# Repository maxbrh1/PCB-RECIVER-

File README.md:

# PCB-RECIVER-

ONETAP Reciver is my pcb

CC1101EM_868_915MHz_3_0_0 Is Ti's refrence design with the cc1101

Please see Schematic Onetap reciver.pdf

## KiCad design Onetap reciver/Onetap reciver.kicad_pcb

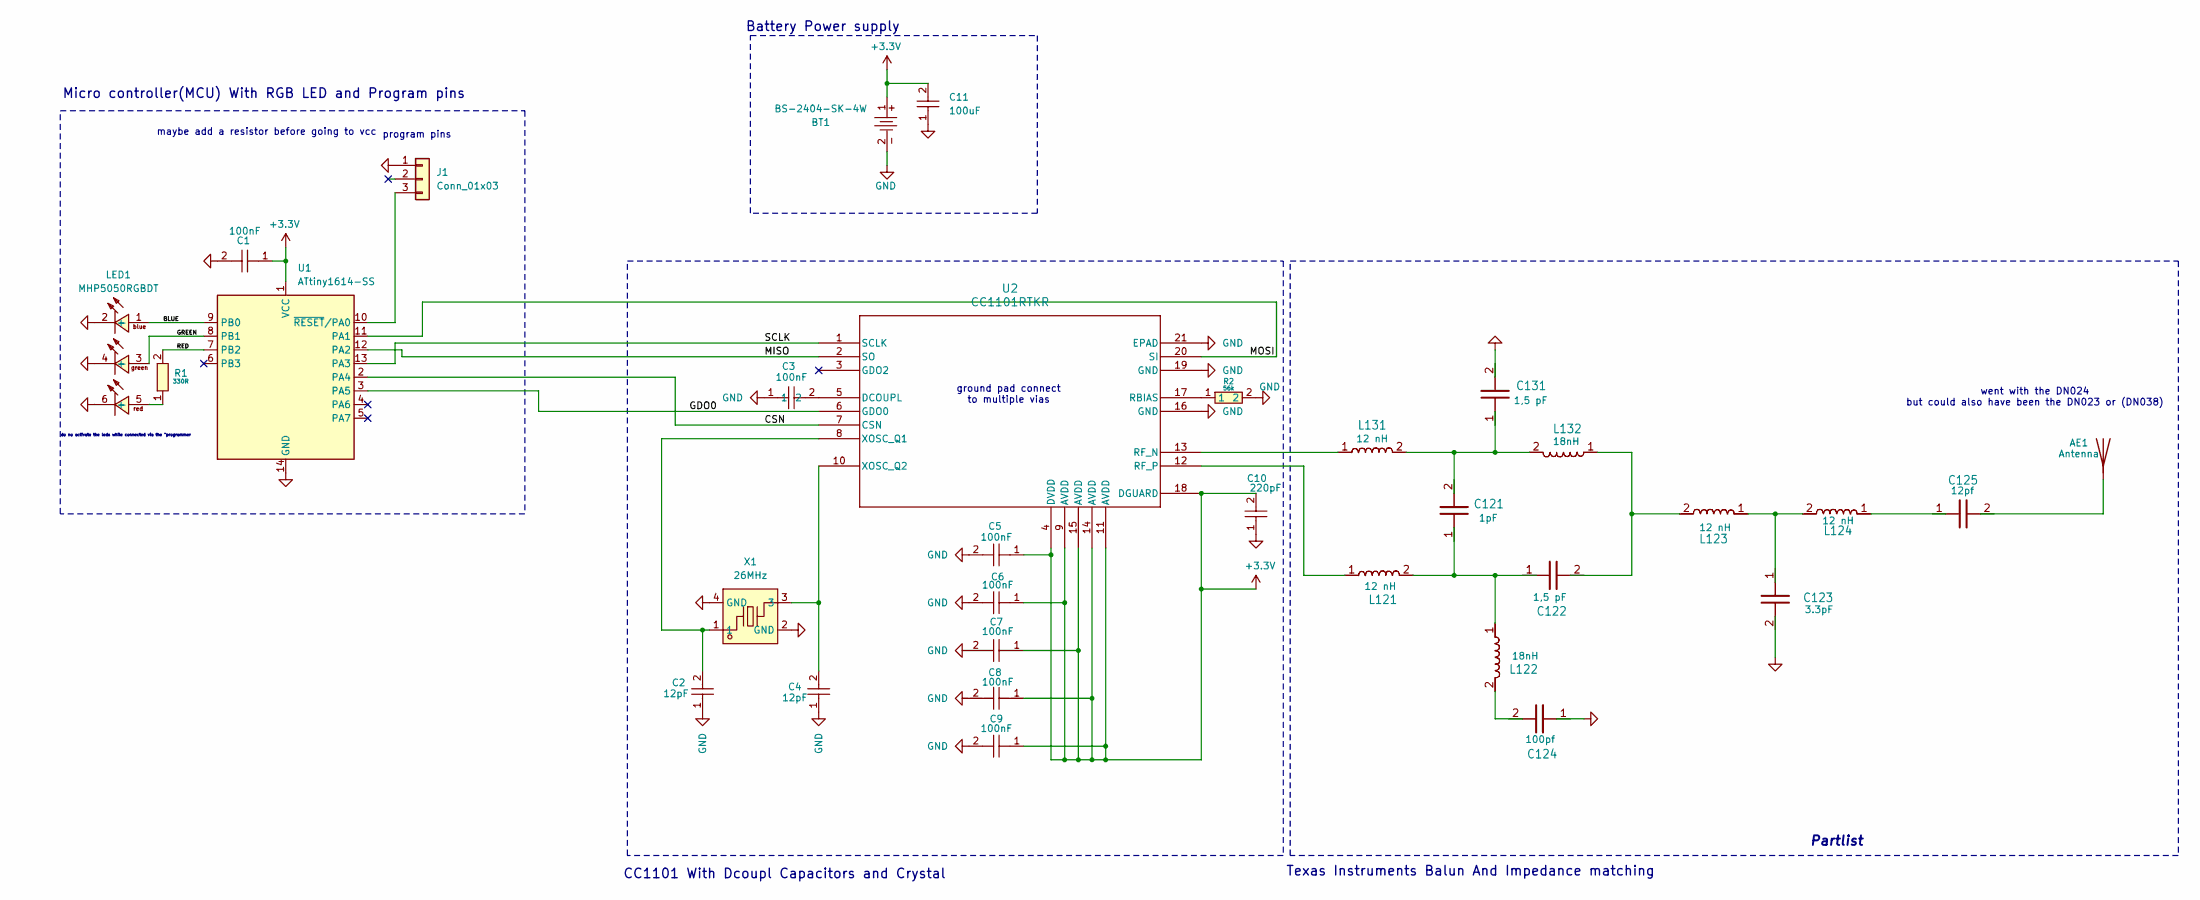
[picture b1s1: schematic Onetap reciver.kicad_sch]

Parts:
AE1: Antenna; DN024
BT1: BS-2404-SK-4W; BAT-SMD_BS-2404-SK-4W; MPN BS-2404-SK-4W; LCSC Part C19089132
C1, C3: 100nF; C0603; MPN CL10B104KB8NNNC; LCSC Part C1591
C2, C4: 12pF; C0603; MPN CL10C120JB8NNNC; LCSC Part C38523
C5, C6, C7, C8, C9: 100nF; G-155_MUR; DigiKey Part Number 490-6321-2-ND - Tape & Reel (TR) 490-63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
C10: 220pF; C0603; MPN CL10B221KB8NNNC; LCSC Part C1603
C11: 100uF; C1206; MPN CL31A107MQHNNNE; LCSC Part C15008
C121: 1pF; TI_0402_RF; Part Name C_1P0_0402_NP0_C_50
C122, C131: 1,5 pF; TI_0402_RF; Part Name C_1P5_0402_NP0_C_50
C123: 3.3pF; TI_0402_RF; Part Name C_3P3_0402_NP0_C_50
C124: 100pf; TI_0402_RF; Part Name C_100P_0402_NP0_J_50
C125: 12pf; TI_0402_RF; Part Name C_12P_0402_NP0_J_50
J1: Conn_01x03; PinHeader_1x03_P2.54mm_Vertical
L121, L123, L124, L131: 12 nH; TI_0402_RF; Mouser Part Number 81-LQW15AN12NJ00D
L122, L132: 18nH; TI_0402_RF; Mouser Part Number 81-LQW15AN18NJ00D
LED1: MHP5050RGBDT; LED-ARRAY-SMD_6P-L5.0-W5.0-TR-RD; MPN MHP5050RGBDT; LCSC Part C409780
R1: 330R; R0603; MPN RS-03K3300FT; LCSC Part C125768
R2: 56k; R0402; MPN RC0402FR-0756KL; LCSC Part C114756
U1: ATtiny1614-SS; SOIC-14_3.9x8.7mm_P1.27mm
U2: CC1101RTKR; QFN50P400X400X100-21N-D
X1: 26MHz; CRYSTAL-SMD_4P-L2.5-W2.0-BL; MPN CM4026M00009T8188026; LCSC Part C2933028

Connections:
+3.3V: BT1.1, C1.1, C5.1, C6.1, C7.1, C8.1, C9.1, C10.2, C11.2, U1.1 (VCC), U2.4 (DVDD), U2.9 (AVDD), U2.11 (AVDD), U2.14 (AVDD), U2.15 (AVDD), U2.18 (DGUARD)
/BLUE: LED1.1 (+), U1.9 (PB0)
/CSN: U1.2 (PA4), U2.7 (CSN)
/GDO0: U1.3 (PA5), U2.6 (GDO0)
/GREEN: LED1.3 (+), U1.8 (PB1)
/MISO: U1.12 (PA2), U2.2 (SO)
/MOSI: U1.11 (PA1), U2.20 (SI)
/RED: R1.2, U1.7 (PB2)
/SCLK: U1.13 (PA3), U2.1 (SCLK)
GND: BT1.2, C1.2, C2.1, C3.1, C4.1, C5.2, C6.2, C7.2, C8.2, C9.2, C10.1, C11.1, C123.2, C124.1, C131.2, J1.1, LED1.2 (-), LED1.4 (-), LED1.6 (-), R2.2, U1.14 (GND), U2.16 (GND), U2.19 (GND), U2.21 (EPAD), X1.2 (GND), X1.4 (GND)
unnamed: AE1.1 (A_1), C125.2
unnamed: C121.1, C122.1, L121.2, L122.1
unnamed: C121.2, C131.1, L131.2, L132.2
unnamed: C122.2, L123.2, L132.1
unnamed: C123.1, L123.1, L124.2
unnamed: C124.2, L122.2
unnamed: C125.1, L124.1
unnamed: J1.3, U1.10 (~RESET/PA0)
unnamed: LED1.5 (+), R1.1
unnamed: C3.2, U2.5 (DCOUPL)
unnamed: R2.1, U2.17 (RBIAS)
unnamed: L131.1, U2.13 (RF_N)
unnamed: L121.1, U2.12 (RF_P)
unnamed: C2.2, U2.8 (XOSC_Q1), X1.1
unnamed: C4.2, U2.10 (XOSC_Q2), X1.3

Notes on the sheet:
maybe add a resistor before going to vcc
program pins
CC1101 With Dcoupl Capacitors and Crystal
Micro controller(MCU) With RGB LED and Program pins
Battery Power supply
went with the DN024 but could also have been the DN023 or (DN038)
Texas Instruments Balun And Impedance matching
do no activate the leds while connected via the "programmer
ground pad connect to multiple vias
Partlist

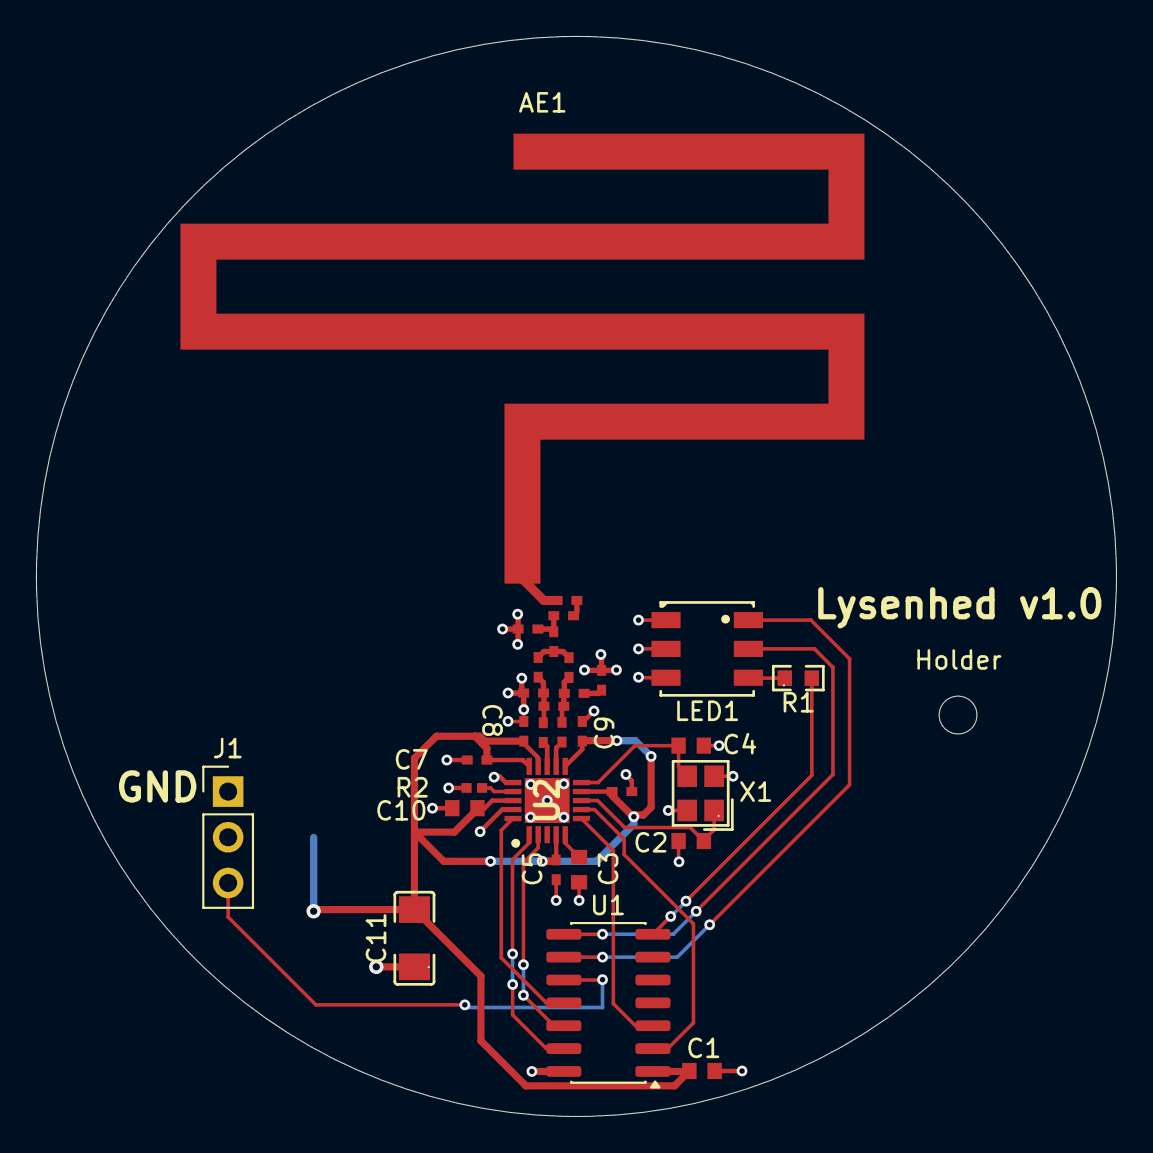
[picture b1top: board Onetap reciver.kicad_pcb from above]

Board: 2 copper layers, 60.0 x 60.0 mm, 33 parts (1 on the bottom side), 25 nets.

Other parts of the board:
Holder: MountingHole_2.1mm

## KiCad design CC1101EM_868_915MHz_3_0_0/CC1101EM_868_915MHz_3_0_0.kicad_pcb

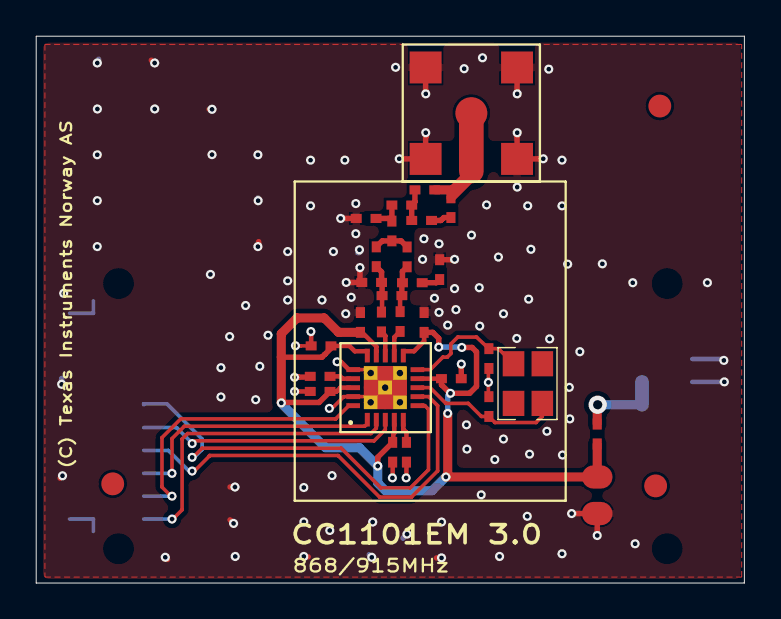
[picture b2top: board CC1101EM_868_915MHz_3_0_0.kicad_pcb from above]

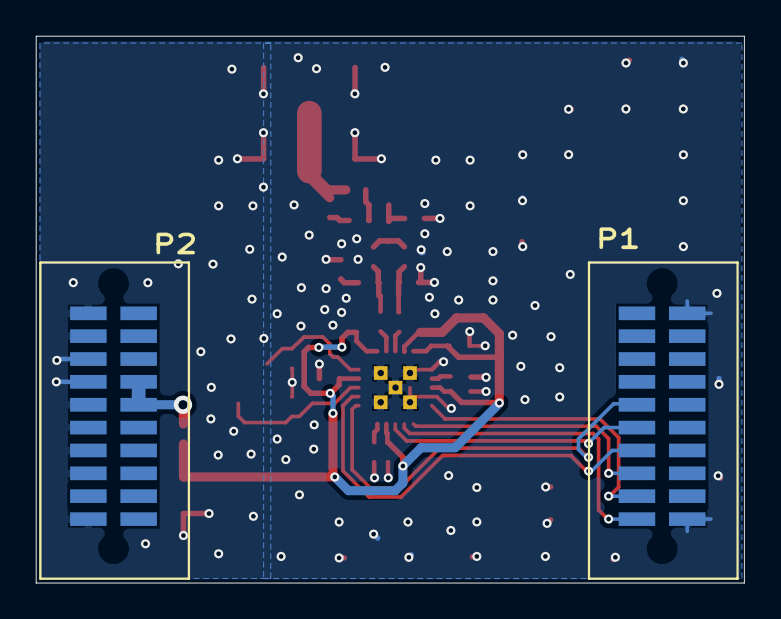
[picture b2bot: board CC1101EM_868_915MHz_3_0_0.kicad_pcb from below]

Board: 2 copper layers, 39.3 x 30.4 mm, 34 parts (2 on the bottom side), 23 nets.

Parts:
C1: C_1U_0805_X7R_K_16; 0805 (reflow)
C41, C51, C91, C111, C141, C151, C181: C_100N_0402_X5R_K_10; 0402 (REFLOW)
C81, C125: C_12P_0402_NP0_J_50; 0402 (REFLOW)
C101: C_15P_0402_NP0_J_50; 0402 (REFLOW)
C121: C_1P0_0402_NP0_C_50; 0402 (REFLOW)
C122, C131: C_1P5_0402_NP0_C_50; 0402 (REFLOW)
C123: C_3P3_0402_NP0_C_50; 0402 (REFLOW)
C124: C_100P_0402_NP0_J_50; 0402 (REFLOW)
C126: C_47P_0402_NP0_J_50; 0402 (REFLOW)
FM1, FM2, FM3: FIDUCIAL_MARK; FIDUCAL_MARK
L1: L_BEAD_102_0402; 0402 (REFLOW)
L121, L123, L124, L131: L_12N_0402_J_LQW; 0402 (REFLOW)
L122, L132: L_18N_0402_J_LQW; 0402 (REFLOW)
L125: L_3N3_0402_J; 0402 (REFLOW)
P1, P2: SMD_SOCKET_2x10; SFM SMD Socket 2x10
P3: SMA_SMD; SMA_SMD (Straight)
R171: R_56K_0402_F; 0402 (REFLOW)
U1: CC1101; QLP20 (Reflow)
X1: X_26.000/50/10; XTAL_SMD_3_2x2_5 (3.2 x 2.5 mm)

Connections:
CSn: P1.14, U1.7
GDO0: P1.10, U1.6
GDO2: P1.12, U1.3
GND: C1.2, C41.2, C51.2, C81.2, C91.2, C101.2, C111.2, C123.2, C124.1, C131.2, C141.2, C151.2, C181.2, P1.1, P1.19, P2.2, P2.4, P2.6, P2.8, P2.10, P2.12, P2.14, P2.16, P2.20, P3.2, P3.3, P3.4, P3.5, R171.2, U1.16, U1.19, U1.21, U1.22, U1.23, U1.24, U1.25, U1.26, U1.27, U1.28
unnamed: C51.1, U1.5
unnamed: C101.1, U1.10, X1.3
unnamed: C121.1, C122.1, L121.2, L122.1
unnamed: C121.2, C131.1, L131.2, L132.2
unnamed: C122.2, L123.2, L132.1
unnamed: L1.2, P2.7, P2.9
unnamed: C124.2, L122.2
unnamed: C123.1, L123.1, L124.2
unnamed: C125.1, C126.1, L124.1
unnamed: C126.2, L125.1
unnamed: C125.2, L125.2, P3.1
unnamed: R171.1, U1.17
unnamed: L121.1, U1.12
unnamed: L131.1, U1.13
unnamed: C81.1, U1.8, X1.1
SCLK: P1.16, U1.1
SI: P1.18, U1.20
SO: P1.20, U1.2
VDD: C1.1, C41.1, C91.1, C111.1, C141.1, C151.1, C181.1, L1.1, U1.4, U1.9, U1.11, U1.14, U1.15, U1.18
